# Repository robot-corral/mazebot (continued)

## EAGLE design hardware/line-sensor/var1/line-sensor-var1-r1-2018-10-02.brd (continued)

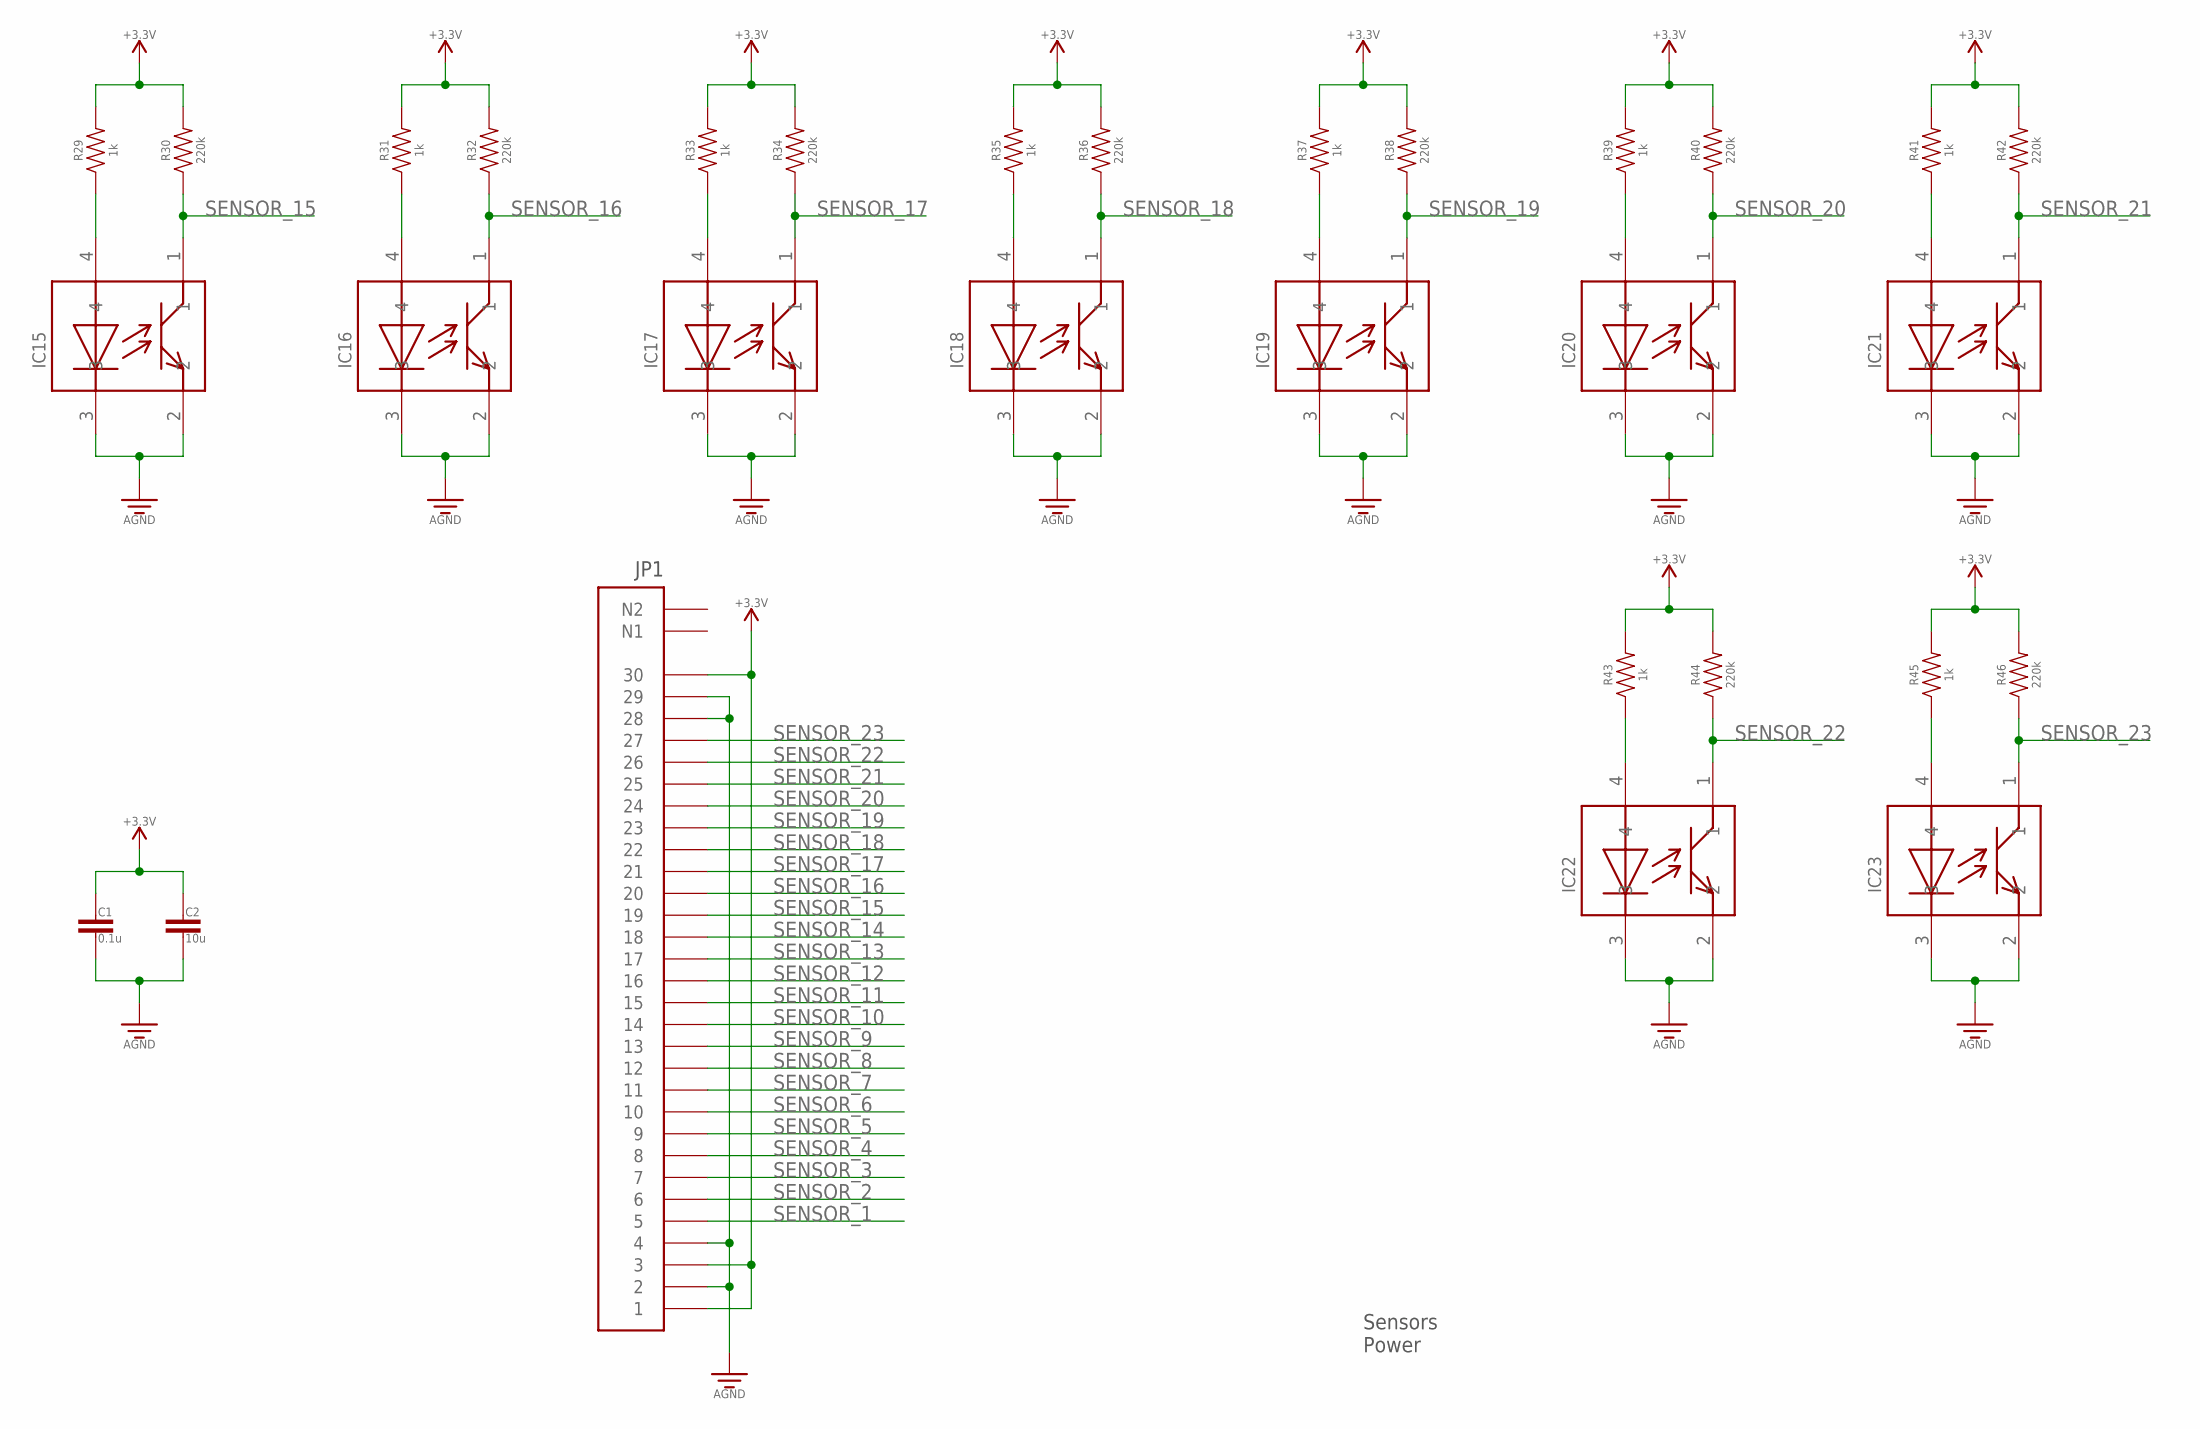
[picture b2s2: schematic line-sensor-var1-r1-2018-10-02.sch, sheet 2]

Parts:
C1: 0.1u; CAPACITOR-0603
C2: 10u; CAPACITOR-0603
IC15, IC16, IC17, IC18, IC19, IC20, IC21, IC22, IC23: GP2S60
JP1: MOLEX-502046-3070
R29, R31, R33, R35, R37, R39, R41, R43, R45: 1k; RESISTOR-0603
R30, R32, R34, R36, R38, R40, R42, R44, R46: 220k; RESISTOR-0603

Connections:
3V3: C1.1, C2.1, JP1.1, JP1.3, JP1.30, R29.P$2 (2), R30.P$2 (2), R31.P$2 (2), R32.P$2 (2), R33.P$2 (2), R34.P$2 (2), R35.P$2 (2), R36.P$2 (2), R37.P$2 (2), R38.P$2 (2), R39.P$2 (2), R40.P$2 (2), R41.P$2 (2), R42.P$2 (2), R43.P$2 (2), R44.P$2 (2), R45.P$2 (2), R46.P$2 (2); also elsewhere on the board
AGND: C1.2, C2.2, IC15.2, IC15.3, IC16.2, IC16.3, IC17.2, IC17.3, IC18.2, IC18.3, IC19.2, IC19.3, IC20.2, IC20.3, IC21.2, IC21.3, IC22.2, IC22.3, IC23.2, IC23.3, JP1.2, JP1.4, JP1.28, JP1.29; also elsewhere on the board
unnamed: IC15.4, R29.P$1 (1)
unnamed: IC16.4, R31.P$1 (1)
unnamed: IC17.4, R33.P$1 (1)
unnamed: IC18.4, R35.P$1 (1)
unnamed: IC19.4, R37.P$1 (1)
unnamed: IC20.4, R39.P$1 (1)
unnamed: IC21.4, R41.P$1 (1)
unnamed: IC22.4, R43.P$1 (1)
unnamed: IC23.4, R45.P$1 (1)
SENSOR_1: JP1.5; also elsewhere on the board
SENSOR_2: JP1.6; also elsewhere on the board
SENSOR_3: JP1.7; also elsewhere on the board
SENSOR_4: JP1.8; also elsewhere on the board
SENSOR_5: JP1.9; also elsewhere on the board
SENSOR_6: JP1.10; also elsewhere on the board
SENSOR_7: JP1.11; also elsewhere on the board
SENSOR_8: JP1.12; also elsewhere on the board
SENSOR_9: JP1.13; also elsewhere on the board
SENSOR_10: JP1.14; also elsewhere on the board
SENSOR_11: JP1.15; also elsewhere on the board
SENSOR_12: JP1.16; also elsewhere on the board
SENSOR_13: JP1.17; also elsewhere on the board
SENSOR_14: JP1.18; also elsewhere on the board
SENSOR_15: IC15.1, JP1.19, R30.P$1 (1)
SENSOR_16: IC16.1, JP1.20, R32.P$1 (1)
SENSOR_17: IC17.1, JP1.21, R34.P$1 (1)
SENSOR_18: IC18.1, JP1.22, R36.P$1 (1)
SENSOR_19: IC19.1, JP1.23, R38.P$1 (1)
SENSOR_20: IC20.1, JP1.24, R40.P$1 (1)
SENSOR_21: IC21.1, JP1.25, R42.P$1 (1)
SENSOR_22: IC22.1, JP1.26, R44.P$1 (1)
SENSOR_23: IC23.1, JP1.27, R46.P$1 (1)

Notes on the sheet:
Sensors Power

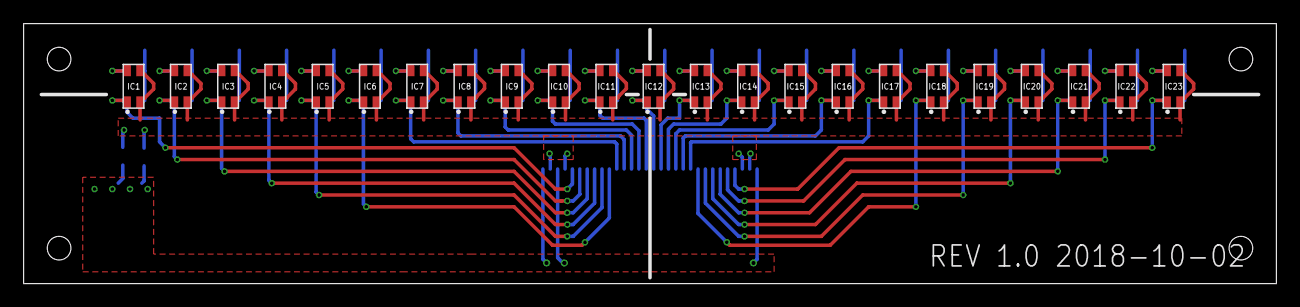
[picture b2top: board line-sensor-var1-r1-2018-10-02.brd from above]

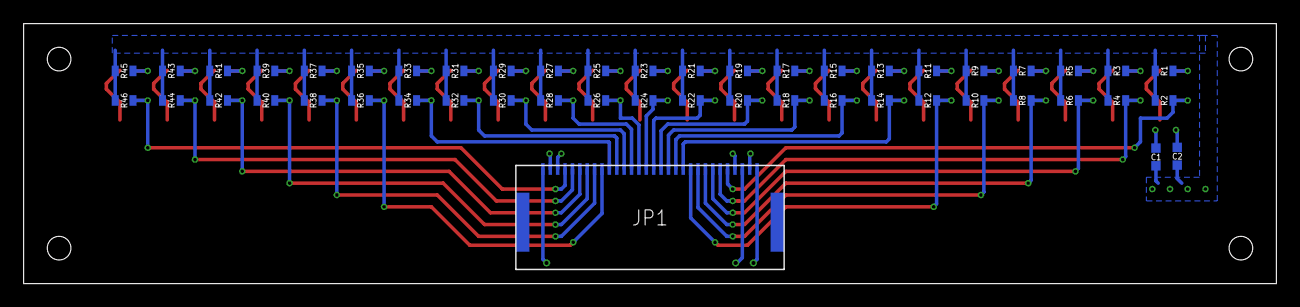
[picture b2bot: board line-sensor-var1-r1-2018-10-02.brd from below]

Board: 2 copper layers, 106.0 x 22.0 mm, 72 parts (49 on the bottom side), 48 nets.

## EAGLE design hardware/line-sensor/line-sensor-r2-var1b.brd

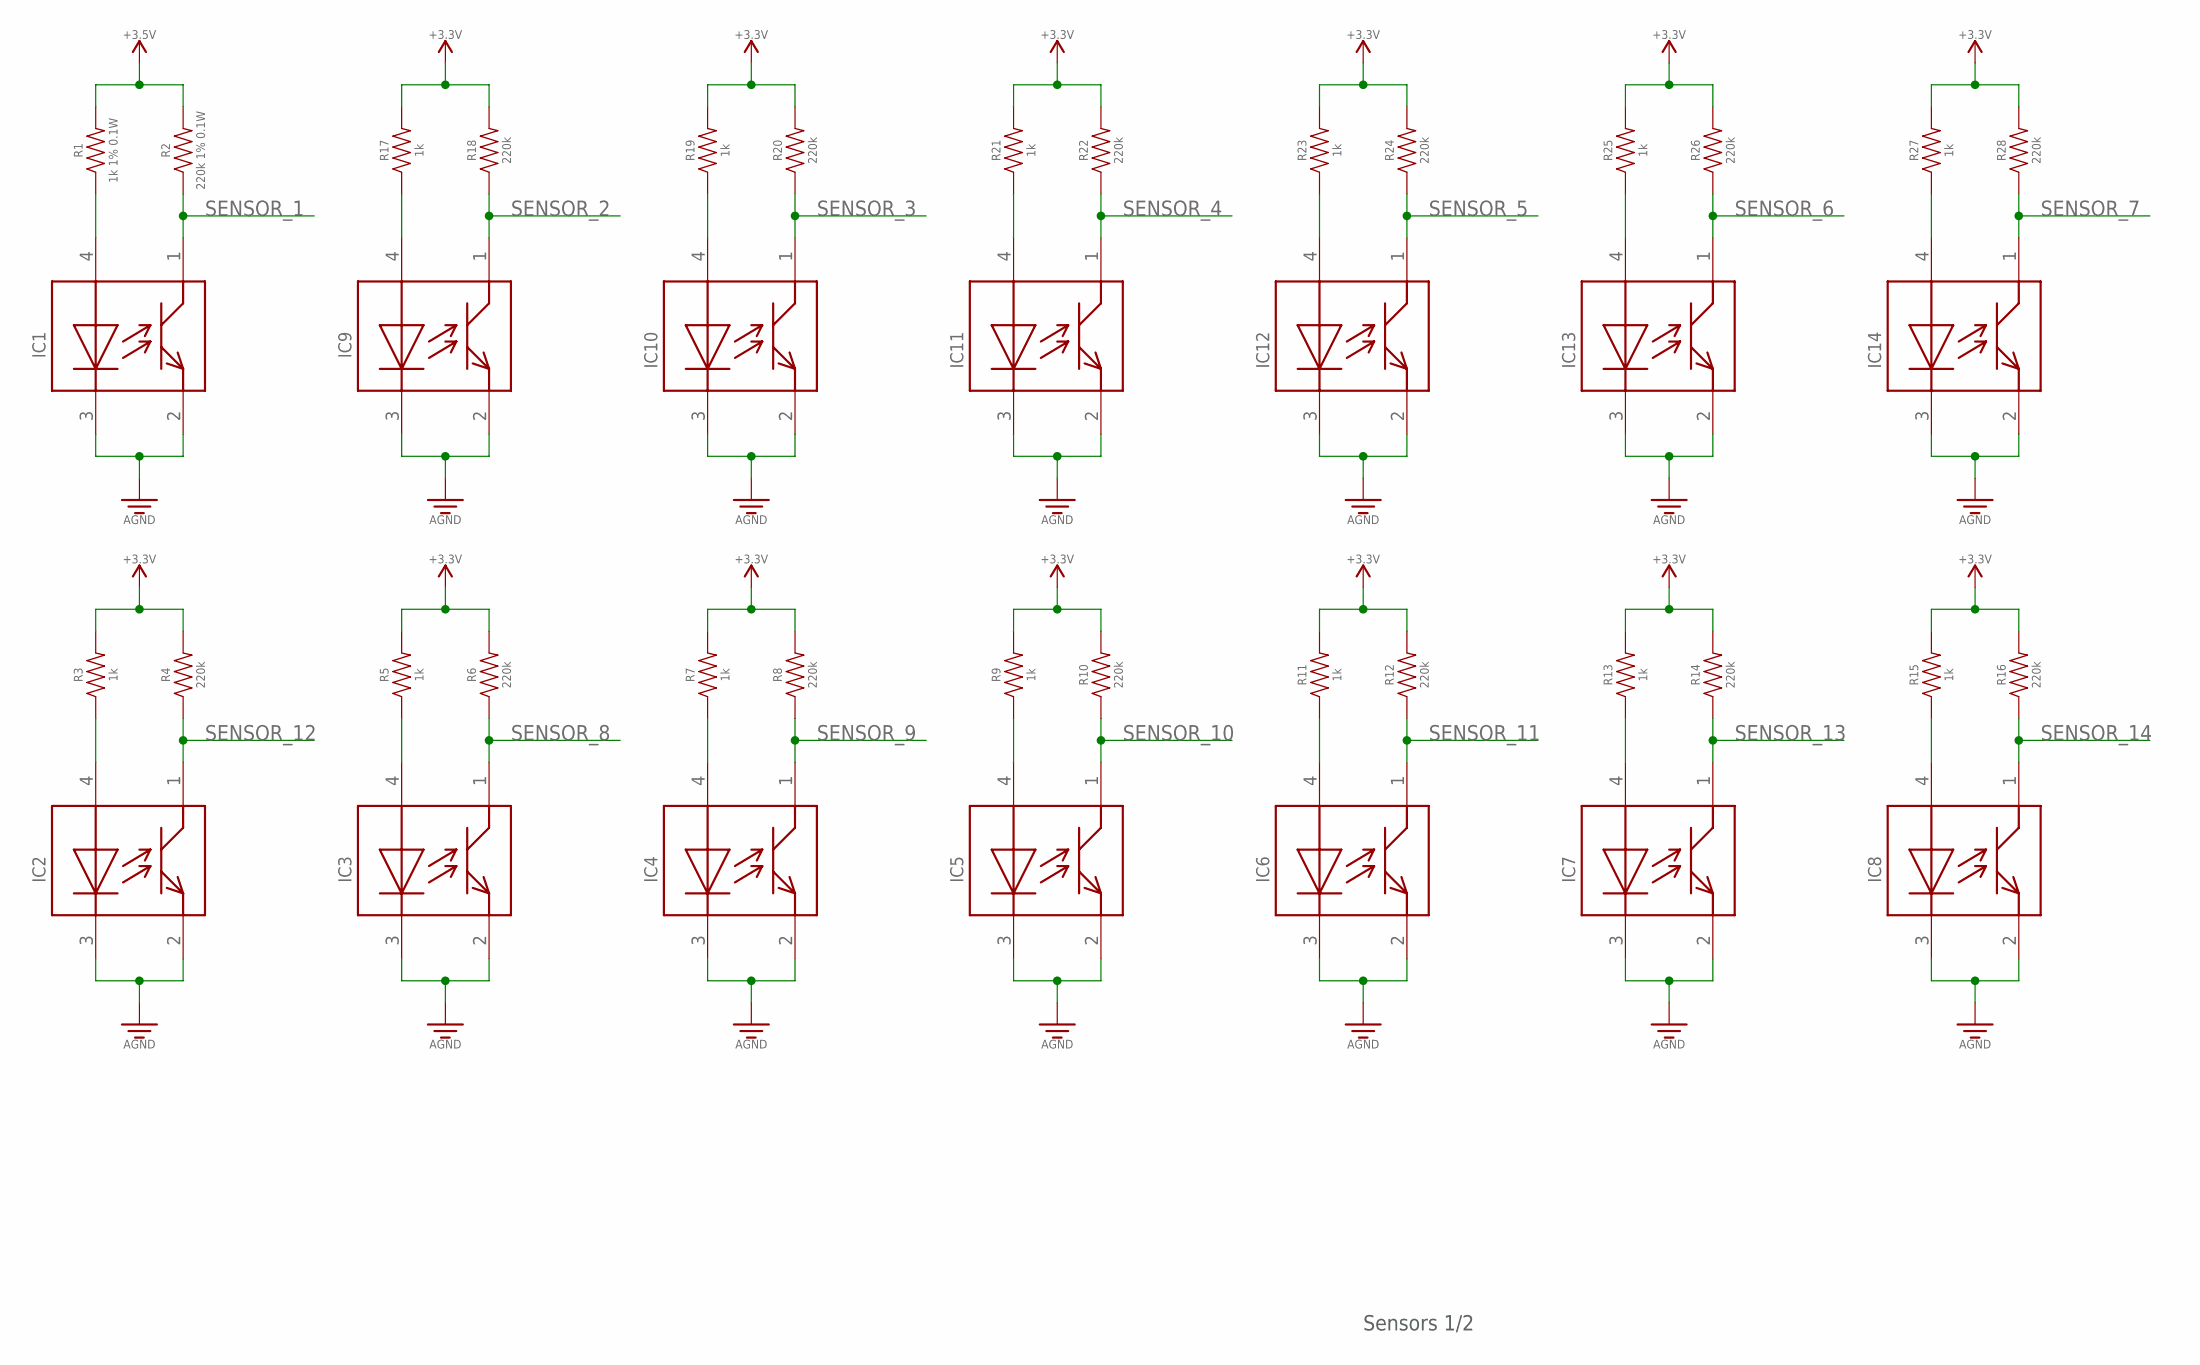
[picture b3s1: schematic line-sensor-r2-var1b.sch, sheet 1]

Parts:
IC1, IC2, IC3, IC4, IC5, IC6, IC7, IC8, IC9, IC10, IC11, IC12, IC13, IC14: GP2S60
R1: 1k 1% 0.1W; RESISTOR-0603
R2: 220k 1% 0.1W; RESISTOR-0603
R3, R5, R7, R9, R11, R13, R15, R17, R19, R21, R23, R25, R27: 1k; RESISTOR-0603
R4, R6, R8, R10, R12, R14, R16, R18, R20, R22, R24, R26, R28: 220k; RESISTOR-0603

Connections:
GND: IC1.2, IC1.3, IC2.2, IC2.3, IC3.2, IC3.3, IC4.2, IC4.3, IC5.2, IC5.3, IC6.2, IC6.3, IC7.2, IC7.3, IC8.2, IC8.3, IC9.2, IC9.3, IC10.2, IC10.3, IC11.2, IC11.3, IC12.2, IC12.3, IC13.2, IC13.3, IC14.2, IC14.3; also elsewhere on the board
unnamed: IC9.4, R17.P$1 (1)
unnamed: IC1.4, R1.P$1 (1)
unnamed: IC10.4, R19.P$1 (1)
unnamed: IC11.4, R21.P$1 (1)
unnamed: IC12.4, R23.P$1 (1)
unnamed: IC13.4, R25.P$1 (1)
unnamed: IC14.4, R27.P$1 (1)
unnamed: IC3.4, R5.P$1 (1)
unnamed: IC4.4, R7.P$1 (1)
unnamed: IC5.4, R9.P$1 (1)
unnamed: IC6.4, R11.P$1 (1)
unnamed: IC2.4, R3.P$1 (1)
unnamed: IC7.4, R13.P$1 (1)
unnamed: IC8.4, R15.P$1 (1)
SENSOR_1: IC1.1, R2.P$1 (1); also elsewhere on the board
SENSOR_2: IC9.1, R18.P$1 (1); also elsewhere on the board
SENSOR_3: IC10.1, R20.P$1 (1); also elsewhere on the board
SENSOR_4: IC11.1, R22.P$1 (1); also elsewhere on the board
SENSOR_5: IC12.1, R24.P$1 (1); also elsewhere on the board
SENSOR_6: IC13.1, R26.P$1 (1); also elsewhere on the board
SENSOR_7: IC14.1, R28.P$1 (1); also elsewhere on the board
SENSOR_8: IC3.1, R6.P$1 (1); also elsewhere on the board
SENSOR_9: IC4.1, R8.P$1 (1); also elsewhere on the board
SENSOR_10: IC5.1, R10.P$1 (1); also elsewhere on the board
SENSOR_11: IC6.1, R12.P$1 (1); also elsewhere on the board
SENSOR_12: IC2.1, R4.P$1 (1); also elsewhere on the board
SENSOR_13: IC7.1, R14.P$1 (1); also elsewhere on the board
SENSOR_14: IC8.1, R16.P$1 (1); also elsewhere on the board
VDD: R1.P$2 (2), R2.P$2 (2), R3.P$2 (2), R4.P$2 (2), R5.P$2 (2), R6.P$2 (2), R7.P$2 (2), R8.P$2 (2), R9.P$2 (2), R10.P$2 (2), R11.P$2 (2), R12.P$2 (2), R13.P$2 (2), R14.P$2 (2), R15.P$2 (2), R16.P$2 (2), R17.P$2 (2), R18.P$2 (2), R19.P$2 (2), R20.P$2 (2), R21.P$2 (2), R22.P$2 (2), R23.P$2 (2), R24.P$2 (2), R25.P$2 (2), R26.P$2 (2), R27.P$2 (2), R28.P$2 (2); also elsewhere on the board

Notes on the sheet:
Sensors 1/2

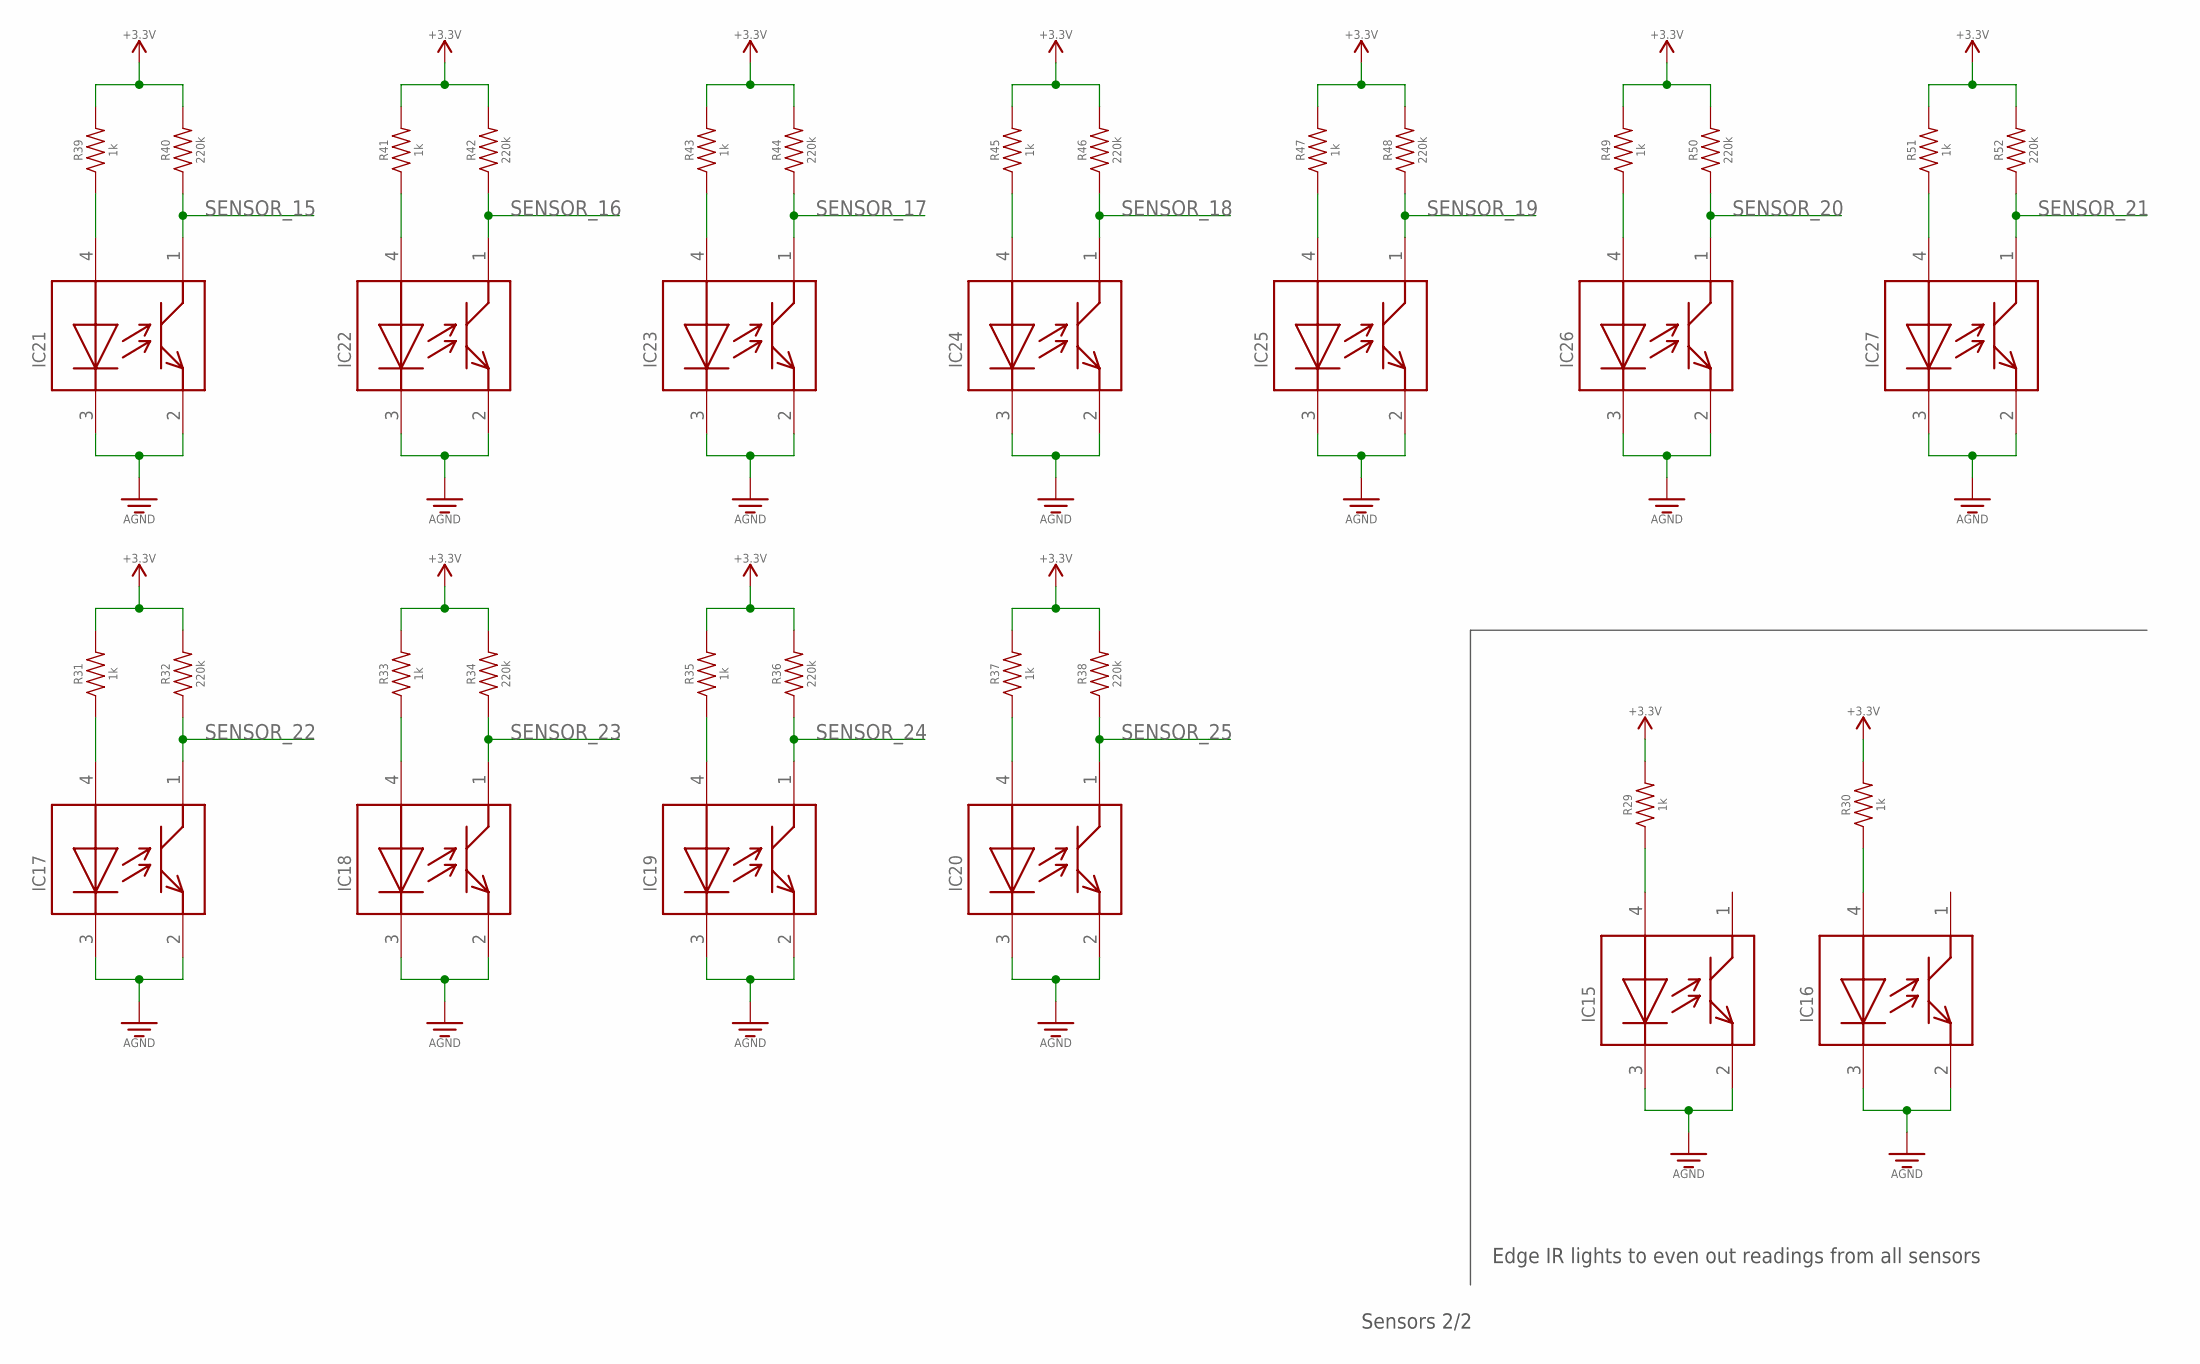
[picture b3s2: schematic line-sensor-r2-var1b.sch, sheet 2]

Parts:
IC15, IC16, IC17, IC18, IC19, IC20, IC21, IC22, IC23, IC24, IC25, IC26, IC27: GP2S60
R29, R30, R31, R33, R35, R37, R39, R41, R43, R45, R47, R49, R51: 1k; RESISTOR-0603
R32, R34, R36, R38, R40, R42, R44, R46, R48, R50, R52: 220k; RESISTOR-0603

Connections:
GND: IC15.2, IC15.3, IC16.2, IC16.3, IC17.2, IC17.3, IC18.2, IC18.3, IC19.2, IC19.3, IC20.2, IC20.3, IC21.2, IC21.3, IC22.2, IC22.3, IC23.2, IC23.3, IC24.2, IC24.3, IC25.2, IC25.3, IC26.2, IC26.3, IC27.2, IC27.3; also elsewhere on the board
unnamed: IC21.4, R39.P$1 (1)
unnamed: IC22.4, R41.P$1 (1)
unnamed: IC23.4, R43.P$1 (1)
unnamed: IC24.4, R45.P$1 (1)
unnamed: IC25.4, R47.P$1 (1)
unnamed: IC26.4, R49.P$1 (1)
unnamed: IC27.4, R51.P$1 (1)
unnamed: IC17.4, R31.P$1 (1)
unnamed: IC18.4, R33.P$1 (1)
unnamed: IC19.4, R35.P$1 (1)
unnamed: IC20.4, R37.P$1 (1)
unnamed: IC16.4, R30.P$1 (1)
unnamed: IC15.4, R29.P$1 (1)
SENSOR_15: IC21.1, R40.P$1 (1); also elsewhere on the board
SENSOR_16: IC22.1, R42.P$1 (1); also elsewhere on the board
SENSOR_17: IC23.1, R44.P$1 (1); also elsewhere on the board
SENSOR_18: IC24.1, R46.P$1 (1); also elsewhere on the board
SENSOR_19: IC25.1, R48.P$1 (1); also elsewhere on the board
SENSOR_20: IC26.1, R50.P$1 (1); also elsewhere on the board
SENSOR_21: IC27.1, R52.P$1 (1); also elsewhere on the board
SENSOR_22: IC17.1, R32.P$1 (1); also elsewhere on the board
SENSOR_23: IC18.1, R34.P$1 (1); also elsewhere on the board
SENSOR_24: IC19.1, R36.P$1 (1); also elsewhere on the board
SENSOR_25: IC20.1, R38.P$1 (1); also elsewhere on the board
VDD: R29.P$2 (2), R30.P$2 (2), R31.P$2 (2), R32.P$2 (2), R33.P$2 (2), R34.P$2 (2), R35.P$2 (2), R36.P$2 (2), R37.P$2 (2), R38.P$2 (2), R39.P$2 (2), R40.P$2 (2), R41.P$2 (2), R42.P$2 (2), R43.P$2 (2), R44.P$2 (2), R45.P$2 (2), R46.P$2 (2), R47.P$2 (2), R48.P$2 (2), R49.P$2 (2), R50.P$2 (2), R51.P$2 (2), R52.P$2 (2); also elsewhere on the board

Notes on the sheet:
Sensors 2/2
Edge IR lights to even out readings from all sensors

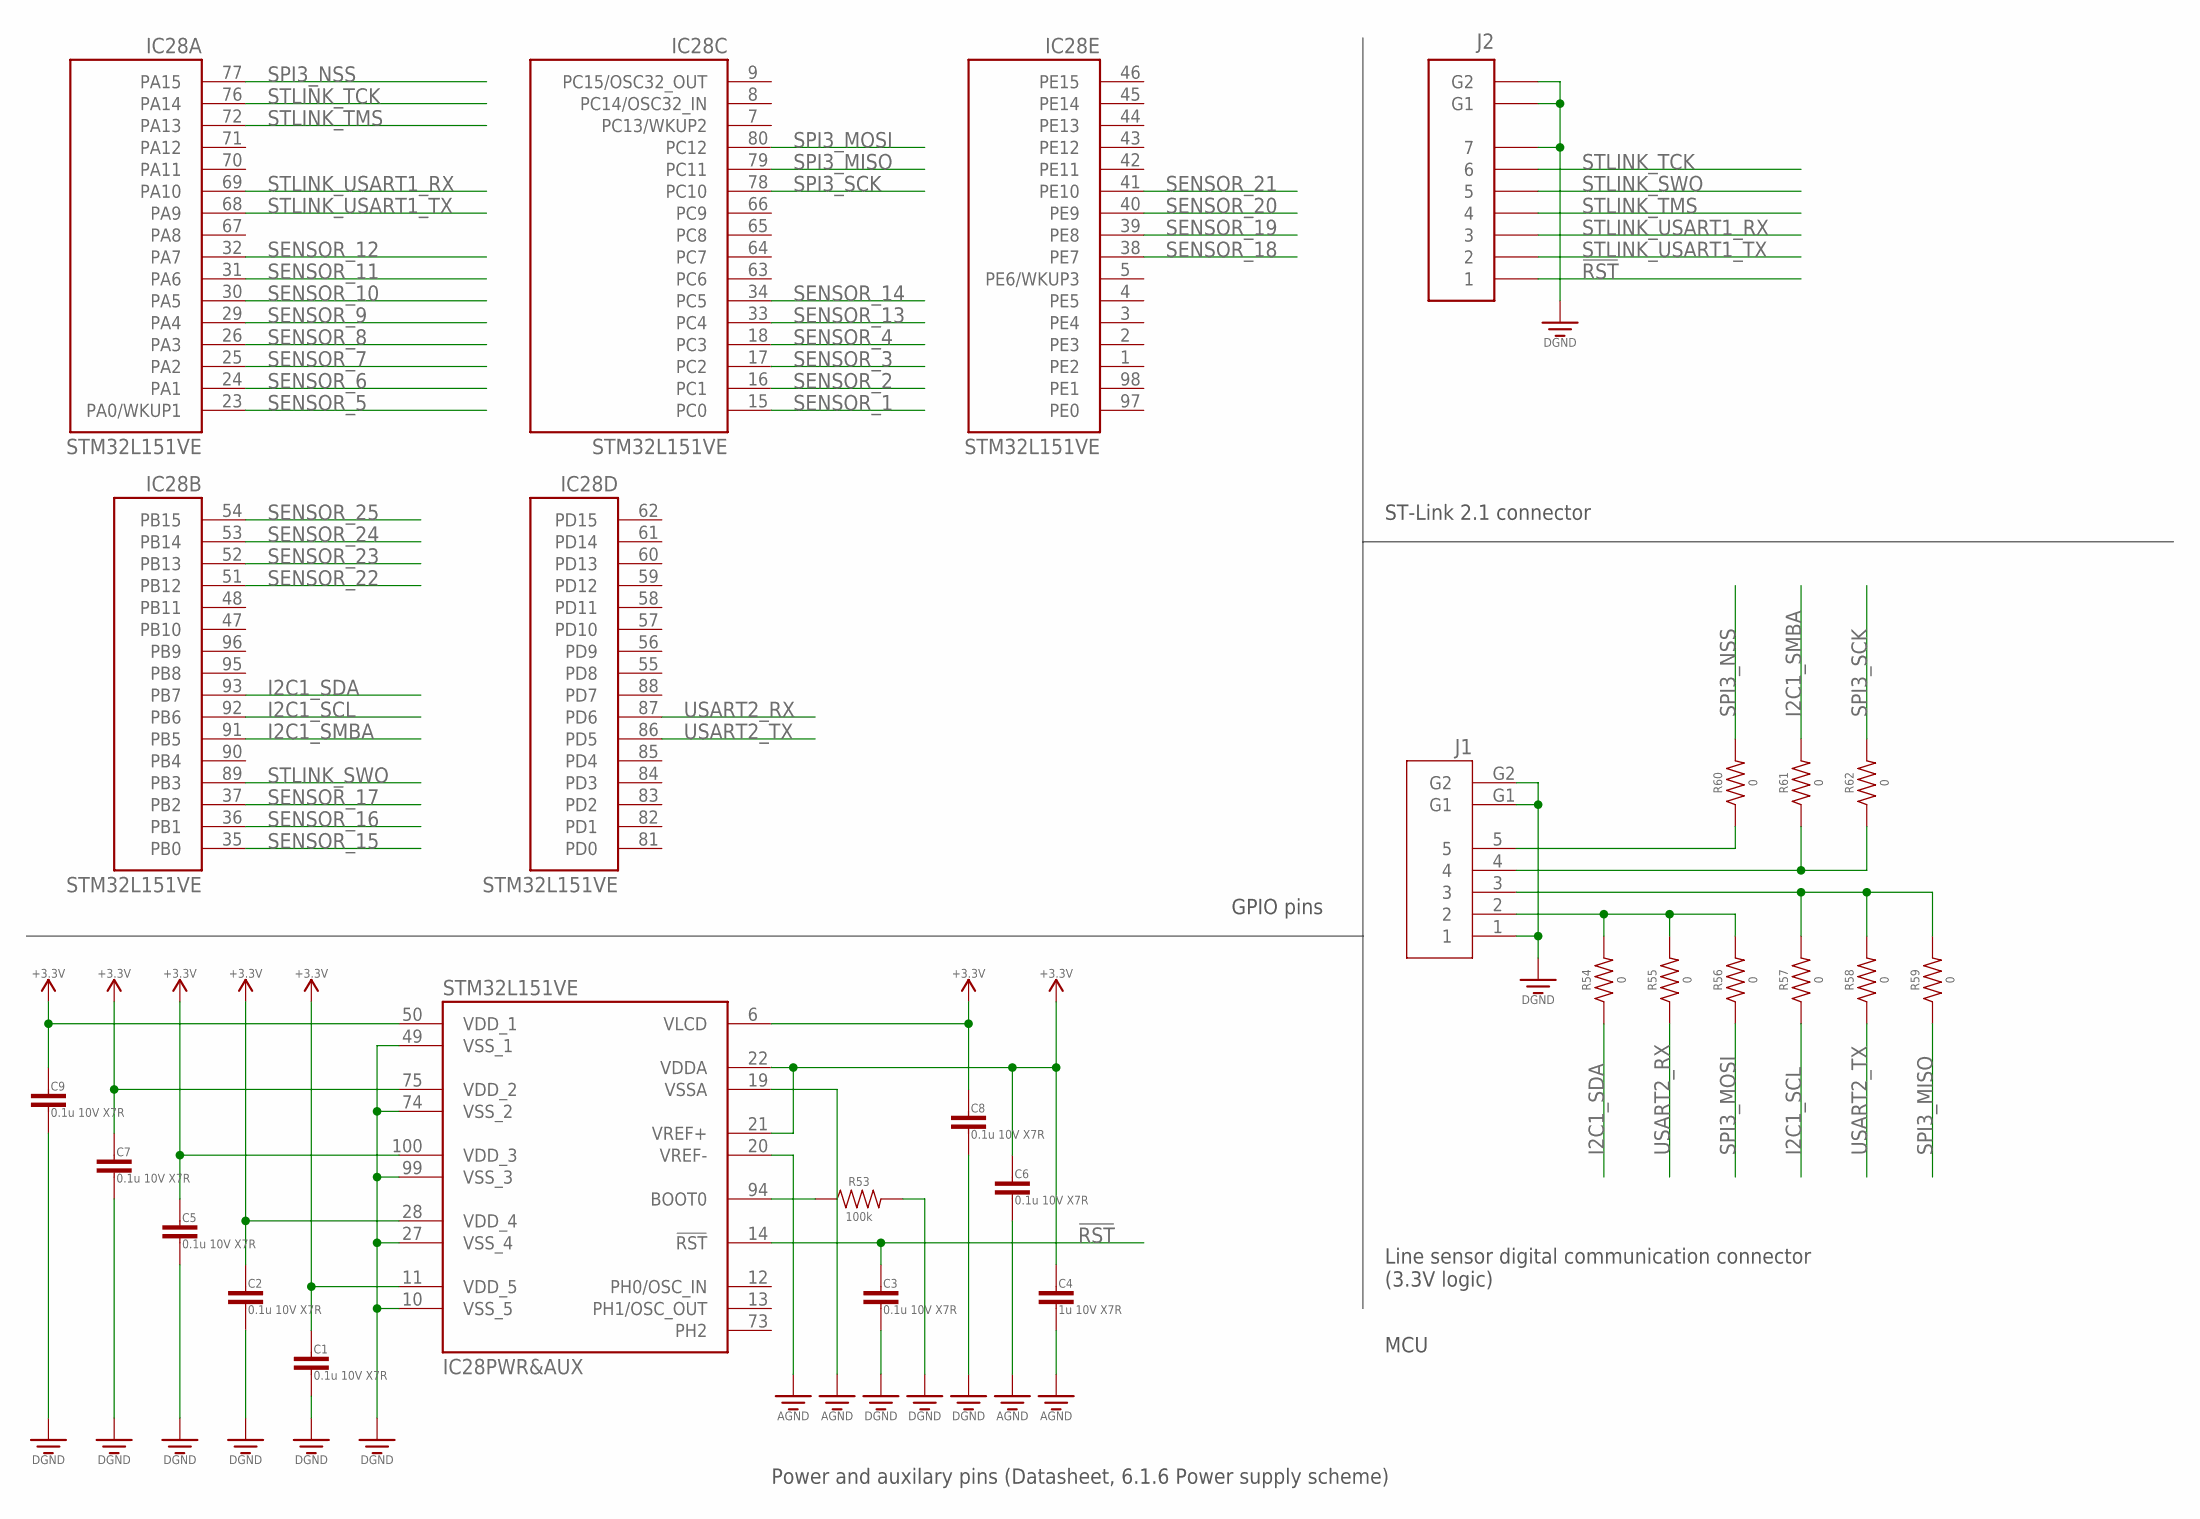
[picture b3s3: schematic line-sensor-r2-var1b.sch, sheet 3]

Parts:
C1, C2, C3, C5, C6, C7, C8, C9: 0.1u 10V X7R; CAPACITOR-0603
C4: 1u 10V X7R; CAPACITOR-0603
IC28: STM32L151VE; LQFP100_14X14
J1: MOLEX-502382-05XX
J2: MOLEX-53261-0771
R53: 100k; RESISTOR-0603
R54, R55, R56, R57, R58, R59, R60, R61, R62: 0; RESISTOR-0603

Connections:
!RST: C3.1, IC28.14 (!RST!), J2.1
BOOT0: IC28.94 (BOOT0), R53.P$1 (1)
GND: C1.2, C2.2, C3.2, C4.2, C5.2, C6.2, C7.2, C8.2, C9.2, IC28.10 (VSS_5), IC28.19 (VSSA), IC28.20 (VREF-), IC28.27 (VSS_4), IC28.49 (VSS_1), IC28.74 (VSS_2), IC28.99 (VSS_3), J1.1, J1.G1, J1.G2, J2.7, J2.G1, J2.G2, R53.P$2 (2); also elsewhere on the board
I2C1_SCL: IC28.92 (PB6), R57.P$1 (1)
I2C1_SDA: IC28.93 (PB7), R54.P$1 (1)
I2C1_SMBA: IC28.91 (PB5), R61.P$2 (2)
unnamed: J1.2, R54.P$2 (2), R55.P$2 (2), R56.P$2 (2)
unnamed: J1.3, R57.P$2 (2), R58.P$2 (2), R59.P$2 (2)
unnamed: J1.4, R61.P$1 (1), R62.P$1 (1)
unnamed: J1.5, R60.P$1 (1)
SENSOR_1: IC28.15 (PC0); also elsewhere on the board
SENSOR_2: IC28.16 (PC1); also elsewhere on the board
SENSOR_3: IC28.17 (PC2); also elsewhere on the board
SENSOR_4: IC28.18 (PC3); also elsewhere on the board
SENSOR_5: IC28.23 (PA0/WKUP1); also elsewhere on the board
SENSOR_6: IC28.24 (PA1); also elsewhere on the board
SENSOR_7: IC28.25 (PA2); also elsewhere on the board
SENSOR_8: IC28.26 (PA3); also elsewhere on the board
SENSOR_9: IC28.29 (PA4); also elsewhere on the board
SENSOR_10: IC28.30 (PA5); also elsewhere on the board
SENSOR_11: IC28.31 (PA6); also elsewhere on the board
SENSOR_12: IC28.32 (PA7); also elsewhere on the board
SENSOR_13: IC28.33 (PC4); also elsewhere on the board
SENSOR_14: IC28.34 (PC5); also elsewhere on the board
SENSOR_15: IC28.35 (PB0); also elsewhere on the board
SENSOR_16: IC28.36 (PB1); also elsewhere on the board
SENSOR_17: IC28.37 (PB2); also elsewhere on the board
SENSOR_18: IC28.38 (PE7); also elsewhere on the board
SENSOR_19: IC28.39 (PE8); also elsewhere on the board
SENSOR_20: IC28.40 (PE9); also elsewhere on the board
SENSOR_21: IC28.41 (PE10); also elsewhere on the board
SENSOR_22: IC28.51 (PB12); also elsewhere on the board
SENSOR_23: IC28.52 (PB13); also elsewhere on the board
SENSOR_24: IC28.53 (PB14); also elsewhere on the board
SENSOR_25: IC28.54 (PB15); also elsewhere on the board
SPI3_MISO: IC28.79 (PC11), R59.P$1 (1)
SPI3_MOSI: IC28.80 (PC12), R56.P$1 (1)
SPI3_NSS: IC28.77 (PA15), R60.P$2 (2)
SPI3_SCK: IC28.78 (PC10), R62.P$2 (2)
STLINK_SWO: IC28.89 (PB3), J2.5
STLINK_TCK: IC28.76 (PA14), J2.6
STLINK_TMS: IC28.72 (PA13), J2.4
STLINK_USART1_RX: IC28.69 (PA10), J2.3
STLINK_USART1_TX: IC28.68 (PA9), J2.2
USART2_RX: IC28.87 (PD6), R55.P$1 (1)
USART2_TX: IC28.86 (PD5), R58.P$1 (1)
VDD: C1.1, C2.1, C4.1, C5.1, C6.1, C7.1, C8.1, C9.1, IC28.6 (VLCD), IC28.11 (VDD_5), IC28.21 (VREF+), IC28.22 (VDDA), IC28.28 (VDD_4), IC28.50 (VDD_1), IC28.75 (VDD_2), IC28.100 (VDD_3); also elsewhere on the board

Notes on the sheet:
MCU
GPIO pins
ST-Link 2.1 connector
Line sensor digital communication connector (3.3V logic)
Power and auxilary pins (Datasheet, 6.1.6 Power supply scheme)

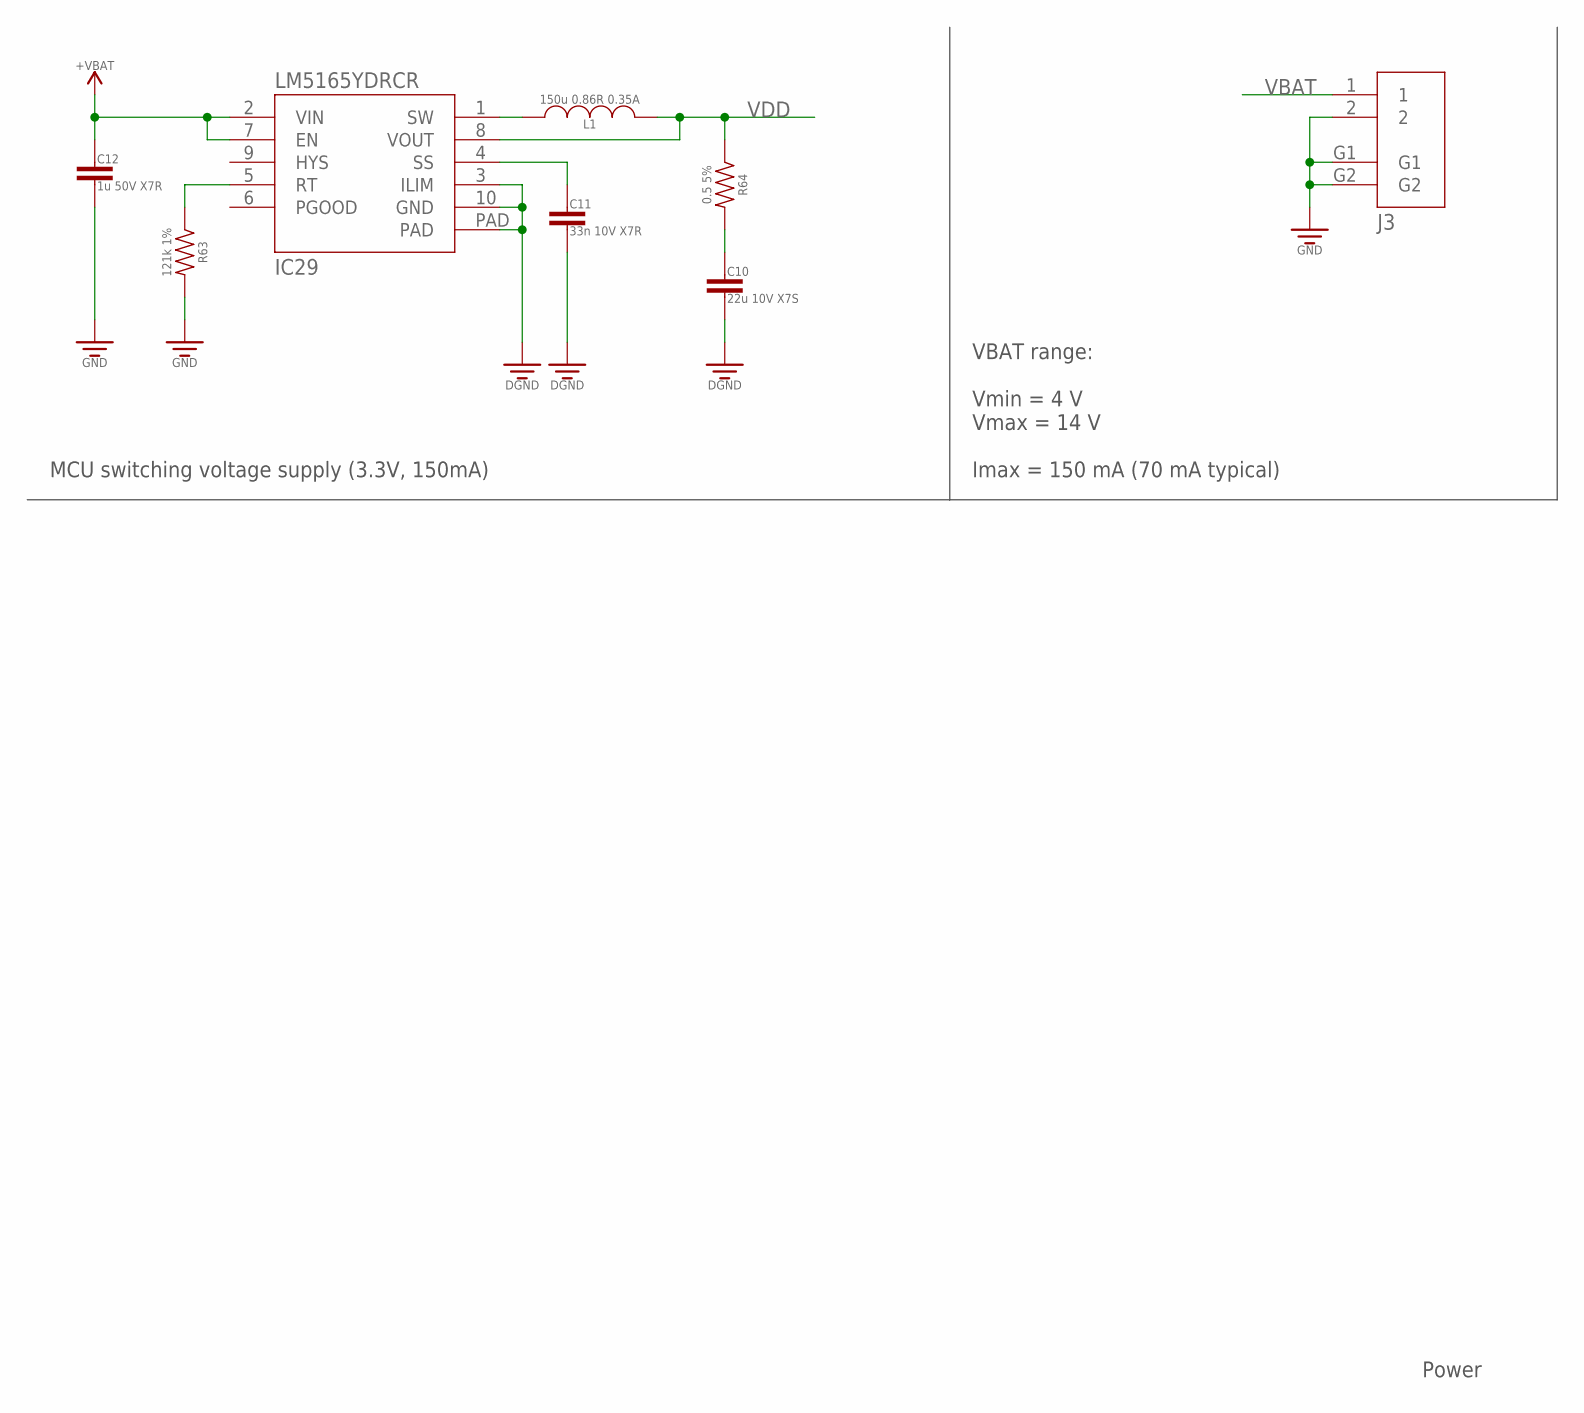
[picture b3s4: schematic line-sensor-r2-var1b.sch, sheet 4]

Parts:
C10: 22u 10V X7S; CAPACITOR-0805
C11: 33n 10V X7R; CAPACITOR-0603
C12: 1u 50V X7R; CAPACITOR-1206
IC29: LM5165YDRCR; VSON-10-0.5MM
J3: MOLEX-502382-02XX
L1: 150u 0.86R 0.35A; PANASONIC-SERIES-H
R63: 121k 1%; RESISTOR-0603
R64: 0.5 5%; RESISTOR-0603

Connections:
GND: C10.2, C11.2, C12.P$2 (2), IC29.3 (ILIM), IC29.10 (GND), IC29.PAD, J3.2, J3.G1, J3.G2, R63.P$2 (2); also elsewhere on the board
IC32_SW: IC29.1 (SW), L1.1
unnamed: IC29.5 (RT), R63.P$1 (1)
unnamed: C11.1, IC29.4 (SS)
unnamed: C10.1, R64.P$2 (2)
VBAT: C12.P$1 (1), IC29.2 (VIN), IC29.7 (EN), J3.1
VDD: IC29.8 (VOUT), L1.2, R64.P$1 (1); also elsewhere on the board

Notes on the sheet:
Power
VBAT range: Vmin = 4 V Vmax = 14 V Imax = 150 mA (70 mA typical)
MCU switching voltage supply (3.3V, 150mA)
